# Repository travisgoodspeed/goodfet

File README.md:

GoodFET
=======

The GoodFET is a nifty little tool for quickly exposing embedded
system buses to userland Python code.  It is no longer under active
development, but I hope that you find it useful nonetheless.

If you are experimenting with the Facedancer USB emulator framework,
you probably want Kate Temkin's fork.  It is available at
https://github.com/ktemkin/Facedancer .

Drivers
-------

For Mac, install XCode, MacPorts, and the FTDI Virtual COM Driver.

For Windows, install Python 2.7 as 32-bit, FTDI VCP Drivers,
and add Python your %PATH% in order to run the scripts in \client.

In Linux, the FTDI drivers are included by default.  Be sure that the
user has permissions for `/dev/ttyUSB0`, which will likely require
adding that user to the dialout group.

Packages
--------

You will need python-serial, wget, gcc-msp430, and curl.  These might
have different names, and the MSP430 compiler might be separated from
its libc implementation.

```sh
sudo apt-get install -y gcc-msp430 msp430-libc curl wget python-serial # Ubuntu Xenial
```

Client
------

First, grab a copy of the client code and link it into
`/usr/local/bin`.

```sh
git clone https://github.com/travisgoodspeed/goodfet/
(cd client && sudo make link)
```

Before using the client, you will need to specify your hardware
revision in the `$client` or `%client%` environment variable.

Firmware
--------

If your GoodFET has not yet been flashed, or if you would like to
develop new firmware features, you will need to compile from scratch.

```sh
cd ~/goodfet/firmware
board=goodfet41 make clean all
```

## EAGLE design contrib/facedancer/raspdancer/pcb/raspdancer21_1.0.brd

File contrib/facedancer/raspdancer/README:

raspdancer11 is a variant of facedancer11 for Raspberry Pi
raspdancer21 is a variant of facedancer21 for Raspberry Pi

More info & contact:
====================
    Philippe Teuwen <phil teuwen.org>
    http://wiki.yobi.be/wiki/Raspdancer

Status:
=======
    Code tested successfully with the Raspdancer11. 
Raspdancer11 PCB not tested yet. Raspdancer11 prototype successfully tested. 
Raspdancer21 PCB not tested yet, design not tested.

Rationale:
==========
    Facedancer11 and Facedancer21 are one-purpose versions of the flexible
GoodFET board. It was well designed to move all the intelligence into the host
controller, not in the embedded uC. Therefore GoodFET part of the Facedancer
designs can be seen as "just" a SPI over UART over USB bridge.
But Raspberry Pi has a native SPI support so let's make dedicated versions.
It's cheaper (you save FT232RL & MSP430F2618TPM).
It's faster (SPI communication with MAX3420E/MAX3421E gets boosted to 26MHz!).
It still uses the same GoodFETMAXUSB.py library.

Construction & components:
==========================
    See pcb/ for Eagle files.
Many thanks to Jean-Christophe Nicaise for the initial Eagle design
and Zac Franken for his many good advices.

Name   Package    Description
------ -------    -----------
U1     LQFP32-08  MAX3420E*                    (* for facedancer11)
U1     TQPF32-5MM MAX3421E**                   (**for facedancer21)
R1     0603       33R USB Serie Resistor
R2     0603       33R USB Serie Resistor
C1     0603       1.0µF Capacitor
C2     0603       0.1µF Decoupling Capacitor
C3     0603       18pF Capacitor
C4     0603       18pF Capacitor
C5     0603       1.0µF Capacitor
Q1     5x3.2      12MHz SMD Crystal, 18pF      (see notes)
USB    USB Mini   Receptacle e.g. UX60-MB-5ST
USB2   USB A      USB-A SMT CONN Receptacle**  (**for facedancer21)
J_RASP 2x13       Receptacle, 2.54mm, 26way    (see notes)

Differences with original Facedancer11/21 (besides removal of GoodFET parts):
* smaller crystal package
* 2x13 connector towards RPi, e.g. a SAMTEC BCS-113-L-D-TE, or even a smaller
  one as 2x6 is enough, but then be the sure to plug the board correctly
  into the larger RPi connector!
* pads on the USB line, in case you want to solder directly a USB cable on it.
* Jumper to allow powering the RPi over this USB but beware:
  You're fuzzing the one which is powering you,
  don't cry if you experience power losses...
  RPi polyfuse is bypassed but power from a *real* USB port should be fine.
* Jumper to allow connecting INT to GPIO24 in case it gets used in the future
* Jumper to allow connecting GPX to GPIO23 in case it gets used in the future

Software:
=========
    Things have been done to be able to reuse the MAXUSB python libraries
written for facedancer. For modern libraries, the only required change is to
switch which object you're instantiating. So, instead of creating a Facedancer
object...

    from Facedancer import *

    sp = GoodFETSerialPort()
    fd = Facedancer(sp, verbose=1)

... create a Raspdancer object:

    from Raspdancer import *

    fd = Raspdancer(verbose=1)

To run the legacy MAXUSB applications, you can replace the original GoodFET.py
by the version provided here. 

Both the modern and legacy support rely on SPI and GPIO libraries; see below.
Code has to be run as root or user with enough rights on SPI & GPIO.

Activating SPI on Raspberry PI
------------------------------
Edit /etc/modprobe.d/raspi-blacklist.conf and comment this line then reboot:
 #blacklist spi-bcm2708

Python SPI library for Raspberry Pi
-----------------------------------
We're using this one:
https://github.com/lthiery/SPI-Py (tested with commit b2c7854c, 2013-04-15)
 wget https://raw.github.com/lthiery/SPI-Py/master/spi.c
 wget https://raw.github.com/lthiery/SPI-Py/master/setup.py
 apt-get install python2.7-dev
 python setup.py build
 Result spi.so is in build/lib.linux-armv6l-2.7/, to be dropped in python path

Python GPIO library for Raspberry Pi
------------------------------------
We're using this one:
https://code.google.com/p/raspberry-gpio-python/
We tested the version v0.4.1a-1 which is pre-installed on Raspbian

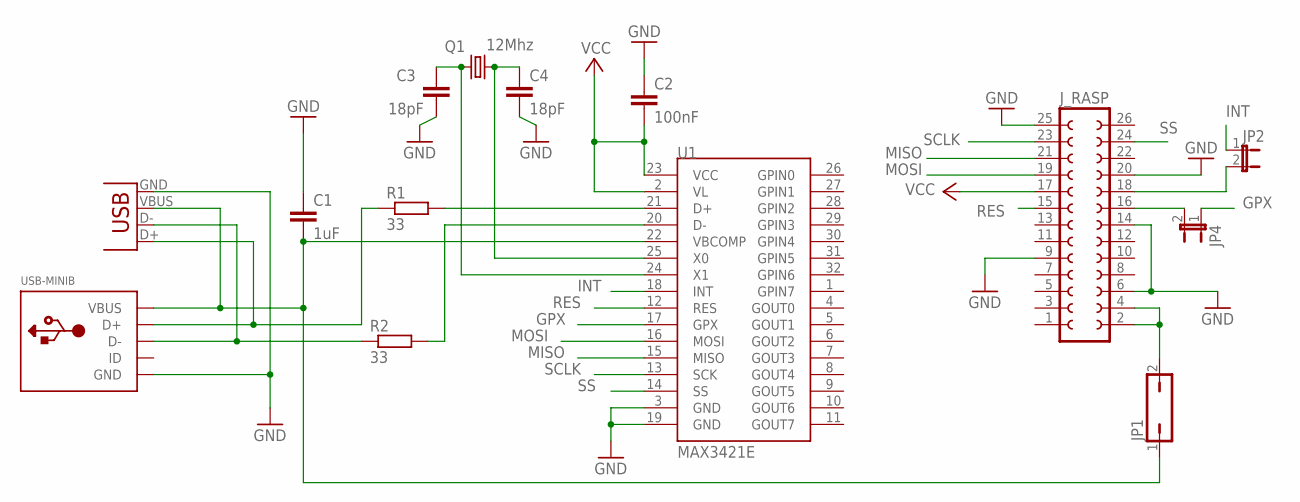
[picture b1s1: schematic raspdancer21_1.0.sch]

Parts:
C1: 1uF; C1206
C2: 100nF; C1206
C3, C4: 18pF; C1206
JP1: JP1Q; JP1
JP2, JP4: JUMPER-2-OLDSMD-NO; SJ_2S-NO
J_RASP: FE13-2
Q1: 12Mhz; CTS406
R1, R2: 33; R1206
U1: MAX3421E; TQFP32-5MM
USB-A: USB-A-S
USB-MINIB: USBMINIB; USB-MINIB

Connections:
D+: R1.2, U1.21 (D+)
D+2: R1.1, USB-A.D+, USB-MINIB.D+
D-: R2.2, U1.20 (D-)
D-2: R2.1, USB-A.D-, USB-MINIB.D-
GND: C1.1, C2.1, C3.2, C4.2, J_RASP.6, J_RASP.9, J_RASP.14, J_RASP.20, J_RASP.25, U1.3 (GND), U1.19 (GND), USB-A.GND, USB-MINIB.GND
GPX: JP4.1, U1.17 (GPX)
GPX2: JP4.2, J_RASP.16
INT: JP2.1, U1.18 (INT)
INT2: JP2.2, J_RASP.18
IX: C4.1, Q1.3 (2), U1.25 (X0)
MISO: J_RASP.21, U1.15 (MISO)
MOSI: J_RASP.19, U1.16 (MOSI)
RES: J_RASP.15, U1.12 (RES)
SCLK: J_RASP.23, U1.13 (SCK)
SS: J_RASP.24, U1.14 (SS)
VBUS: C1.2, JP1.1, U1.22 (VBCOMP), USB-A.VBUS, USB-MINIB.VBUS
VBUS2: JP1.2, J_RASP.2, J_RASP.4
VCC: C2.2, J_RASP.17, U1.2 (VL), U1.23 (VCC)
XO: C3.1, Q1.1, U1.24 (X1)

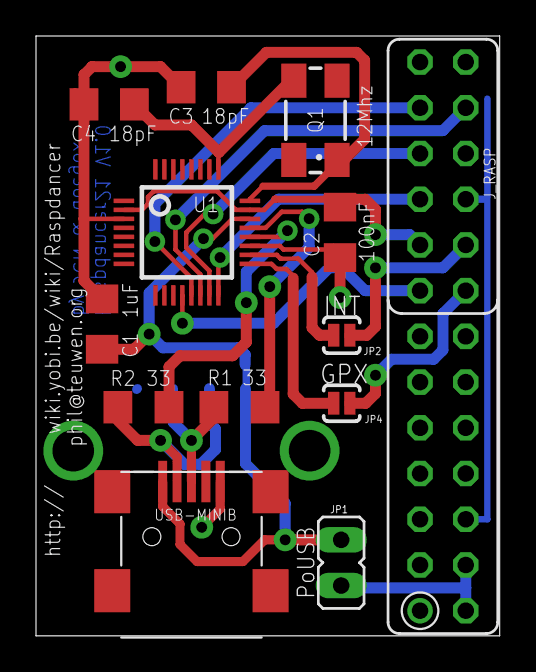
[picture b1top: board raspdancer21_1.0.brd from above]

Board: 2 copper layers, 25.8 x 33.3 mm, 14 parts (1 on the bottom side), 19 nets.

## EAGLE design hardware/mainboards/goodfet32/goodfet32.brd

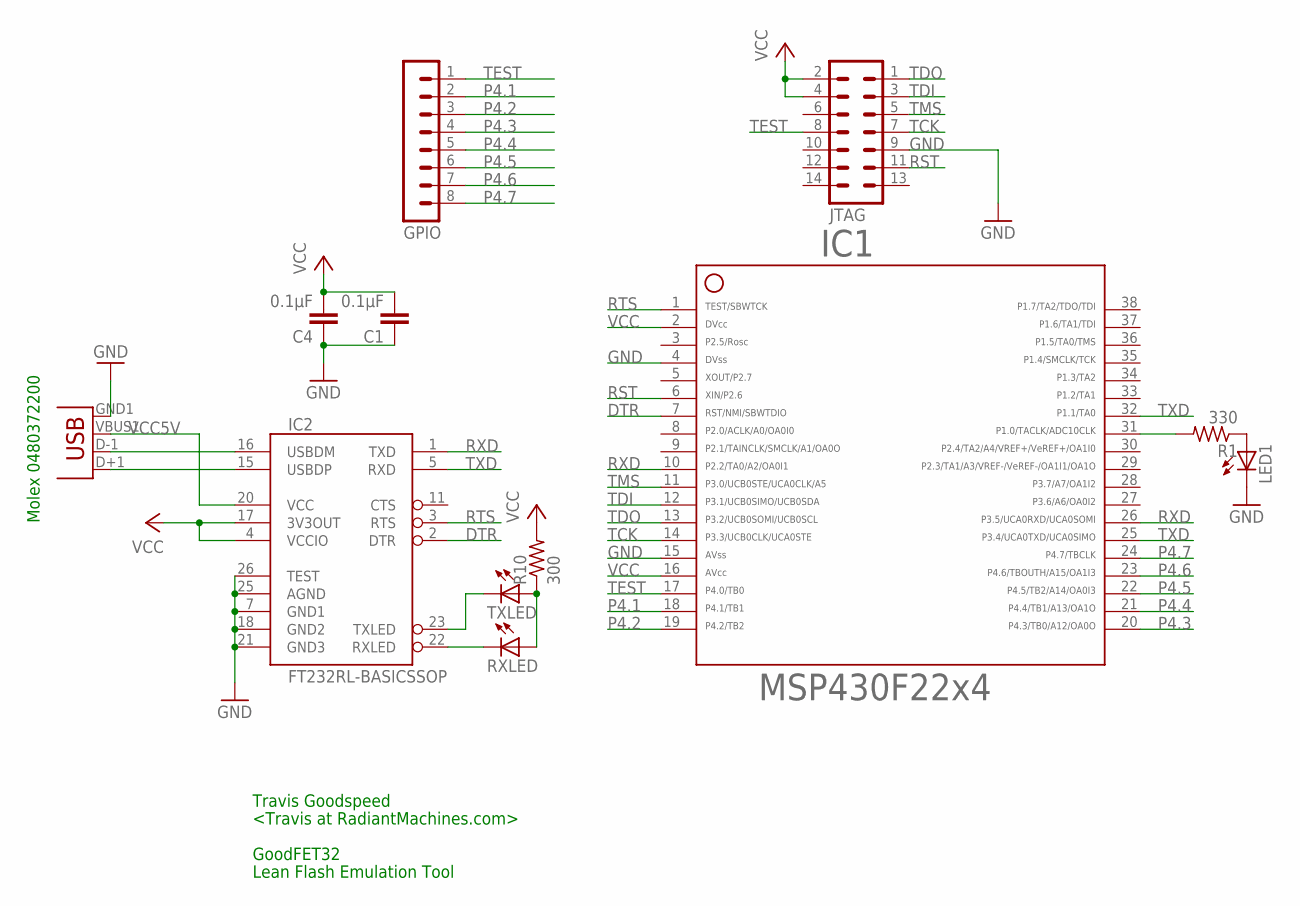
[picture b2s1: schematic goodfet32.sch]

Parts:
C1, C4: 0.1µF; C0603
GPIO: MA08-1
IC1: F22X4---DA38; DA38
IC2: FT232RL-BASICSSOP; SSOP28DB
JP1: USBA-SMD-MALE; USB-A-SMT-MALE
JTAG: MA07-2
LED1: LEDCHIP-LED0603; CHIP-LED0603
R1: 330; R0603
R10: 300; R0603
RXLED: LEDCHIP-LED0603; CHIP-LED0603
TXLED: LEDCHIP-LED0603; CHIP-LED0603

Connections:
DTR: IC1.7, IC2.2 (DTR)
GND: C1.1, C4.1, IC1.4, IC1.15, IC2.7 (GND1), IC2.18 (GND2), IC2.21 (GND3), IC2.25 (AGND), IC2.26 (TEST), JP1.GND1 (GND), JTAG.9, LED1.C
unnamed: IC2.15 (USBDP), JP1.D+1 (D+)
unnamed: IC2.16 (USBDM), JP1.D-1 (D-)
unnamed: IC2.22 (RXLED), RXLED.C
unnamed: IC2.23 (TXLED), TXLED.C
unnamed: R10.1, RXLED.A, TXLED.A
unnamed: IC1.31, R1.2
unnamed: LED1.A, R1.1
P4.1: GPIO.2, IC1.18
P4.2: GPIO.3, IC1.19
P4.3: GPIO.4, IC1.20
P4.4: GPIO.5, IC1.21
P4.5: GPIO.6, IC1.22
P4.6: GPIO.7, IC1.23
P4.7: GPIO.8, IC1.24
RST: IC1.6, JTAG.11
RTS: IC1.1, IC2.3 (RTS)
RXD: IC1.10, IC1.26, IC2.1 (TXD)
TCK: IC1.14, JTAG.7
TDI: IC1.12, JTAG.3
TDO: IC1.13, JTAG.1
TEST: GPIO.1, IC1.17, JTAG.8
TMS: IC1.11, JTAG.5
TXD: IC1.25, IC1.32, IC2.5 (RXD)
VCC: C1.2, C4.2, IC1.2, IC1.16, IC2.4 (VCCIO), IC2.17 (3V3OUT), JTAG.2, JTAG.4, R10.2
VCC5V: IC2.20 (VCC), JP1.VBUS1 (VBUS)

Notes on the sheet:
Travis Goodspeed
<Travis at RadiantMachines.com>
GoodFET32
Lean Flash Emulation Tool
Molex 0480372200

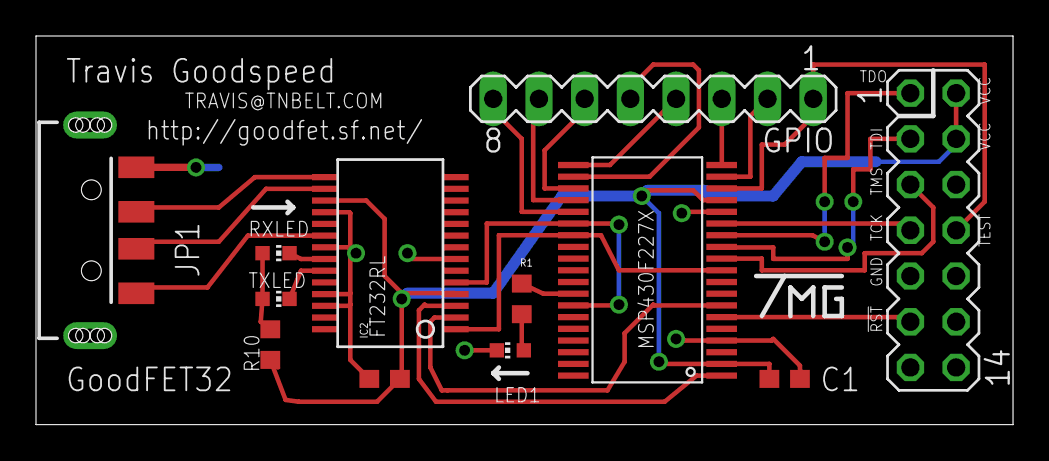
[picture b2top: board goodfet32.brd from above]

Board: 2 copper layers, 54.3 x 21.6 mm, 12 parts (0 on the bottom side), 27 nets.

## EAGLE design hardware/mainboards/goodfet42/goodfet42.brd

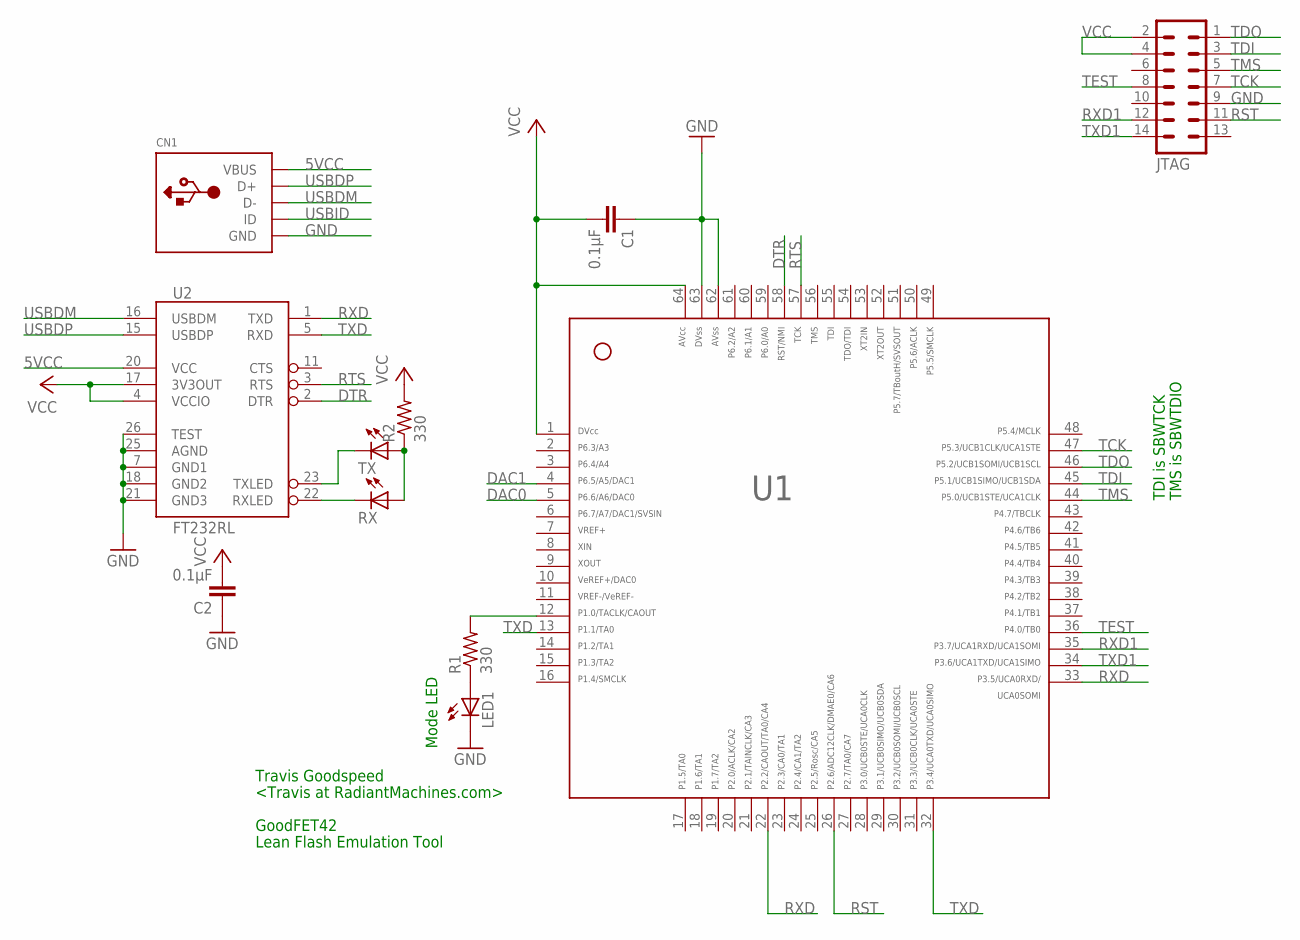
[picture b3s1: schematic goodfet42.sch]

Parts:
C1, C2: 0.1µF; C0603
CN1: USBMINIB; USB-MINIB
JTAG: MA07-2
LED1: LEDCHIP-LED0603; CHIP-LED0603
R1, R2: 330; R0603
RX: LEDCHIP-LED0603; CHIP-LED0603
TX: LEDCHIP-LED0603; CHIP-LED0603
U1: MSP430F2618TPM; PM/PAG64
U2: FT232RL; SSOP28DB

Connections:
5VCC: CN1.VBUS, U2.20 (VCC)
DAC0: U1.5
DAC1: U1.4
DTR: U1.58, U2.2 (DTR)
GND: C1.1, C2.1, CN1.GND, JTAG.9, LED1.C, U1.62, U1.63, U2.7 (GND1), U2.18 (GND2), U2.21 (GND3), U2.25 (AGND), U2.26 (TEST)
unnamed: R1.2, U1.12
unnamed: LED1.A, R1.1
unnamed: RX.C, U2.22 (RXLED)
unnamed: TX.C, U2.23 (TXLED)
unnamed: R2.1, RX.A, TX.A
RST: JTAG.11, U1.26
RTS: U1.57, U2.3 (RTS)
RXD: U1.22, U1.33, U2.1 (TXD)
RXD1: JTAG.12, U1.35
TCK: JTAG.7, U1.47
TDI: JTAG.3, U1.45
TDO: JTAG.1, U1.46
TEST: JTAG.8, U1.36
TMS: JTAG.5, U1.44
TXD: U1.13, U1.32, U2.5 (RXD)
TXD1: JTAG.14, U1.34
USBDM: CN1.D-, U2.16 (USBDM)
USBDP: CN1.D+, U2.15 (USBDP)
USBID: CN1.ID
VCC: C1.2, C2.2, JTAG.2, JTAG.4, R2.2, U1.1, U1.64, U2.4 (VCCIO), U2.17 (3V3OUT)

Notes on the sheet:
TDI is SBWTCK
TMS is SBWTDIO
Mode LED
Travis Goodspeed
<Travis at RadiantMachines.com>
GoodFET42
Lean Flash Emulation Tool

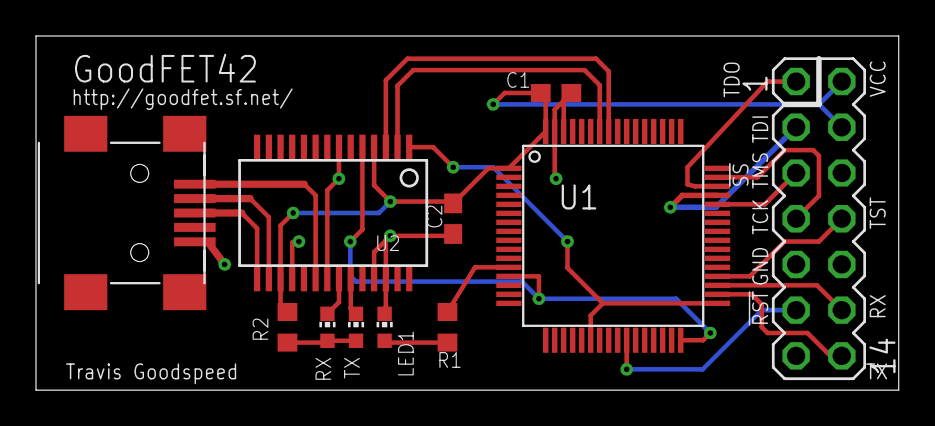
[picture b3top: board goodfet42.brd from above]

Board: 2 copper layers, 47.9 x 19.7 mm, 11 parts (0 on the bottom side), 22 nets.

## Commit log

2014-05-04 Readme file.
2014-05-04 Mainboards.
2014-05-04 Makefile for uploading designs.
2014-05-04 Symbols.
2014-05-04 GIMME board by Ossmann.
2014-05-04 Contrib files.
2014-05-04 Firmware.
2014-05-04 Shellcode for Chipcon devices.
2014-05-04 Client code. Facedancer will be forked out to its own repo.
2014-05-04 Website.
2014-05-04 Instructions.
2014-05-04 Firmware instructions.
2014-05-04 Fixed GoodFET11 support by disabling I2C.
2014-05-04 Github URLs instead of the sourceforge ones.
2014-05-04 URL.
2014-05-05 fixes #4: add a basic spi client also add a git ignore
2014-05-14 goodfet.spiflash can now read/write status register to verify/enable/disable write protection
2014-05-24 Fixed remote file download for Win32. Removed wget dependency.
2014-06-06 Safer file write for downloaded firmware.
2014-06-06 os.sep.join -> os.path.join
2014-06-06 Fixed misuse of os.path.join
2014-06-20 Removed series resistors from GF30 BOM.
2014-06-22 Prebuilt firmware images.
2014-06-23 Facedancer firmware.
2014-07-05 Packaging scripts, imported from the old SVN repo.
2014-07-05 Support for goodthopter12, packages come from git.
2014-09-12 Updated the EM260 functionality. The original clients were cloned from another client (probably the Chipcon SPI) and were not completely functional for the EM260. The EM260's SPI interface provides d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
    cutaway
2014-09-12 Fixed import reference.
    cutaway
2014-10-13 HushCon 2013 badge.
2014-10-23 Fix mutiple command exec in JTAG
    A function was put inside macros to do bitswapping. This leads
    to execute 2 or 4 times the given function which is probably not
    the intended behavior! Thanks 0xf4b for finding and reporting it.
2014-12-16 New spiflash_setstatusflags function
2014-12-16 Fix comment
2014-12-16 Remove useless status overwrite in SPI poke
2014-12-16 add eON EN25F80 SPI ID
2014-12-16 Implement sector erase for SPI flash
2014-12-25 Implemented Dallas/Maxim 1-Wire Bus on pin 8
2014-12-26 Reworked 1-Wire app to match the standard verbs Added temperature sensor support
2014-12-26 Added page documenting one-wire app and client
2015-05-02 Fixed CAN extended id support in packet2parsed
    Fixed extended id support in GoodFETMCPCAN.packet2parsed
2015-08-02 Apimotes v2/3/4 require the 'apimote2' board definition. Added the appropriate aliases.
2015-08-21 improve verbose mode.
2015-08-21 restore default to jtag, not sbw
2015-08-21 prefix vars with sbw as suggested, then move basic routine before its use.
2015-08-21 get rid of useless macros
2015-08-21 add firmware ignores
2015-08-21 remove useless setup calls
2015-08-21 fix typo. Closes #18.
2015-08-21 improve readability
2015-08-21 routines are more coherent with ti spec but tckl pulses are still not ok.
2015-09-08 remove backup files
2015-10-07 Use while loop to attempt USB disconnect in case it fails the first time, or we didn't wait long enough
2015-10-07 Perform self-test on reset to ensure clock is synchronized
2015-12-26 add raw IO access app to the firmware
2015-12-26 add raw IO access client support
2015-12-26 add raw IO access example - 7-segment display
2016-01-31 Call callable descriptors in USBInterface.get_descriptor
2016-02-22 make link now works with paths with spaces
2016-02-28 Updated goodfet.bsl to work on Python3
2016-04-05 pySerial does not support setTimeout in V3. the set / get methods have been replaced in version 2 by properties
2016-04-12 Dump at91 Memory
2016-04-12 dependencies
2016-04-12 Calls for arm9 at91sam7 added
2016-04-15 halt and resume just once
2016-07-01 read data from ep0 when available in control request
2016-08-18 let GOODFET variable set Facedancer device
2016-08-18 add /client/__pycache__ to gitignore
2016-08-18 add a mouse emulation example
2016-08-18 oops, fix some mistakes
2016-08-18 remove extraneous send in SET_IDLE handler
2016-12-22 Add support for the Raspdancer boards using the modern APIs.
2017-05-21 Fixed a signed type warning in CCSPI. No behavioral change.
2017-07-22 Added package names.
2018-06-09 Force Python version for scripts that depend on it
2018-07-28 Fixes for programming the GoodFET42
2018-07-28 Add READBIT and WRITEBIT support to owe (1-wire) app.
2018-07-28 Add SearchROM command to owe (1-Wire) client.
2018-10-23 added command for 4byte read
2018-11-05 Updates the README to direct to Kate's fork of the Facedancer. Close #40.
2018-11-08 Update README.md
    Fixing a typo.
2019-01-28 Fix CCSPI TX ignore last byte
    The CCSPI app had a bug in CCSPI_TX verb, it used the frame length field
    as the length of the entire packet to send. However, according to
    802.15.4 spec it's the length of the payload not including the one byte
    header (see http://www.ti.com/lit/ds/symlink/cc2420.pdf 16.2 - Length
    Field).
    This bug is fixed by using the length provided in the message and not
2019-02-18 Fix CCSPI pokeram functionality
    * Fix a bug in ccspi_pokeram wrong address parameter type
    * Add double strobing of SXOSCON upon setup
    I have no idea WHY the second item is needed but poking the RAM doesn't
    work without it ¯\_(ツ)_/¯
2019-02-26 CCSPI - implemented verb tx wait for rx
    Add verb to ccspi app for sending a packet and waiting for an incoming
    packet.
2020-11-20 Fix for problem in CC2420 read caused by a wrong variable name. This error cause a fail read on data from the CC2420.
2022-01-09 Update goodfet.i2ceeprom
    xxd() function which prints the data expects byte string, not array. Converting what gets appended to.
2022-01-10 Update goodfet.i2ceeprom
    Update readme to show how it works on 16-bit address chips.
2025-03-03 Fix KiCad link
    The previous link went to http://www.kicad-pcb.org/ which now seems to point to some weird gaming site? The official link is kicad.org.

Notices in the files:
parts and their libraries:
SparkFun-Connectors: Licensing: CC v3.0 Share-Alike You are welcome to use this library for commercial purposes.
